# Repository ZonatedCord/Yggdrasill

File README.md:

<div align="center">

# Yggdrasill

**Smart LED plant pot** — custom ESP32 PCB, addressable LEDs, WLED firmware, a modular 3D-printed vase, and a native iOS app with Apple's Liquid Glass design.

</div>

---

## What it is

A tree-shaped plant pot built from three independent pieces that come together into one object:

<table>
<tr>
<td width="33%" valign="top">

### Hardware
`PCB/`

ESP32 board driving WS2812B / SK6812 addressable LEDs, plus the leaf board that carries the LEDs. 5 KiCad projects: 4 base-board projects (dev-kit, bare-chip Rev 1.03, bare-chip Rev 2.0, USB-C) and the leaf (`Foglia`).

</td>
<td width="33%" valign="top">

### 3D print
`3D/`

Modular vase — base, lid, trunk, 3 branches, 9 leaves — joined with bayonet/snap-fit joints. FDM-printable in PETG or PLA. Prototype built in PLA on a Bambu Lab P2S; the supports inside the branches are hard to remove, see [3D/README.md](3D/README.md).

</td>
<td width="33%" valign="top">

### iOS app
`WLED-iOS/`

Liquid Glass redesign (iOS 26) of a WLED controller. mDNS discovery, WebSocket control.

</td>
</tr>
</table>

---

## Assembly preview

<table>
<tr>
<td align="center" width="50%"><b>Leaf insertion</b></td>
<td align="center" width="50%"><b>Branch assembly</b></td>
</tr>
<tr>
<td></td>
<td></td>
</tr>
</table>

---

## Status

**Working prototype built (Oct 2026):** vase, base, lid, 9 leaves and 3 branches printed in PLA on a Bambu Lab P2S, wired with Wago connectors, with 9 LED leaves; the plant lights up. The leaves will be reprinted to hide the visible layer lines.

| Component | Status |
|---|---|
| BaseChipOnly PCB | **Recommended.** Rev 1.03 (`PCB/BaseChipOnly/`) is fabricated and was brought up and tested; it works with workarounds. **Rev 2.0** (`PCB/BaseChipOnly_rev2/`) fixes every bring-up defect, new layout — verified by DRC/ERC and simulation only, **not yet fabricated or tested on hardware** |
| BaseDevKit PCB | Active |
| BaseUSB-C rev0.1 PCB | Early revision |
| Foglia PCB | Active (9 used in the prototype) |
| Modular vase (`3D/STL_stampa/`) | **Prototype built and working** (PLA, Bambu Lab P2S): vase, base, lid, 9 leaves and all 3 branches fit. Joints were tight at first and needed the mating surfaces smoothed. The fit of `TasselloFissaggioPCB.stl` with the PCB in the base is not yet verified. Tip: the supports inside the branches are hard to remove — a dissolvable/dedicated support filament might help (untested); the author cleaned them by hand with a screwdriver and wire. Print plate for the branches in `Rami.3mf`; details in [3D/README.md](3D/README.md) |
| iOS app (Liquid Glass) | In development |

---

## PCB renders

Board renders are generated from the KiCad files.

<table>
<tr>
<td align="center" width="50%"><b>Rev 1.03 &mdash; fabricated, tested</b></td>
<td align="center" width="50%"><b>Rev 2.0 &mdash; not yet fabricated</b></td>
</tr>
<tr>
<td></td>
<td></td>
</tr>
</table>

Bottom side: [Rev 1.03](PCB/BaseChipOnly/render/bottom.png) &middot; [Rev 2.0](PCB/BaseChipOnly_rev2/render/bottom.png). The renders also show the polyfuse and the two buttons (Rev 2.0) as simplified models, not the real components; regenerate them (and the leaf renders) with `python3 PCB/render/make_renders.py` — see [PCB/README.md](PCB/README.md#regenerating-the-renders).

<table align="center">
<tr>
<td align="center"><b>Leaf board (Foglia) &mdash; top</b></td>
<td align="center"><b>Leaf board (Foglia) &mdash; bottom</b></td>
</tr>
<tr>
<td align="center"></td>
<td align="center"></td>
</tr>
</table>

---

## Photos

Photos of the prototype, the electronics and the earlier versions are in the [docs/images/](docs/images/README.md) folder.

---

## What you need

| For | You need |
|---|---|
| The lamp | A 3D printer with about 256 mm of Z height (branches are up to 335 mm long and are printed lying down; prototype: Bambu Lab P2S, 0.4 mm nozzle, PLA) |
| The electronics | A fabricated `BaseChipOnly` PCB (Gerbers in `PCB/<variant>/Esportazione/`), 9 `Foglia` leaf boards, a USB-UART adapter for flashing WLED, a 5 V **4 A** power supply (see power notes in [docs/assembly.md](docs/assembly.md#power-requirements)) |
| Wiring | Thin, long wires and Wago-style splicing connectors (see [docs/3d-printing.md](docs/3d-printing.md#assembly-notes)) |
| Assembly tips | Solder paste stencils for the SMD boards (the leaf board is needed in 9 copies), see [docs/hardware.md](docs/hardware.md#assembly-tips-solder-paste-stencils) |
| PCB editing | **KiCad 9** (the project files are saved with KiCad 9 and do not open in KiCad 8) |
| The app | **Xcode 26** to build (the project is saved with Xcode 26.2); deployment target 16.0 as set in the Xcode project; the Liquid Glass design targets iOS 26 |

## How to build it

1. **Print** the parts from `3D/STL_stampa/` (PLA or PETG, 0.2 mm layers). Orientation, branch plate (`Rami.3mf`), support removal and joint clearances: [docs/3d-printing.md](docs/3d-printing.md) and [3D/README.md](3D/README.md).
2. **Fabricate the PCBs.** Gerbers are in `PCB/<variant>/Esportazione/` (Rev 2.0: `PCB/BaseChipOnly_rev2/Esportazione-2026-09-30/`); upload them to JLCPCB or PCBWay. Variants, BOM and fabrication notes: [docs/hardware.md](docs/hardware.md). The 3D base is designed for `BaseChipOnly` only.
3. **Flash WLED** on the ESP32 and **assemble** the lamp (wiring, base, trunk, branches, leaves, lid): follow [docs/assembly.md](docs/assembly.md) (work in progress). Board details and first power-up: [docs/base-chiponly-pcb.md](docs/base-chiponly-pcb.md).
4. **Control it** from the iOS app below, or from any WLED client.

### iOS app

Build with **Xcode 26** (the project is saved with Xcode 26.2). The app's deployment target is iOS 16.0 as set in the Xcode project; the Liquid Glass styling is the iOS 26 design language.

```bash
git clone --recurse-submodules https://github.com/ZonatedCord/Yggdrasill
open WLED-iOS/wled.xcodeproj
```

> `WLED-iOS/` is a git submodule pointing to the `liquid-glass-redesign` branch of [ZonatedCord/WLED-iOS](https://github.com/ZonatedCord/WLED-iOS) — a fork of [Moustachauve/WLED-iOS](https://github.com/Moustachauve/WLED-iOS) restyled with Apple's Liquid Glass (iOS 26). Already cloned without `--recurse-submodules`? Run `git submodule update --init`. More: [docs/ios-app.md](docs/ios-app.md).

---

## Repository structure

```
Yggdrasill/
├── PCB/               KiCad projects — BaseDevKit, BaseChipOnly (Rev 1.03), BaseChipOnly_rev2 (Rev 2.0), BaseUSB-C_rev0.1, Foglia + footprint library (Impronte/) + render/ (make_renders.py)
├── 3D/                Modular vase — Vaso/ (STEP sources + animations), STL_stampa/ (print-ready STLs + Rami.3mf)
├── WLED-iOS/          iOS app (Liquid Glass, GPL v3) — git submodule → ZonatedCord/WLED-iOS @ liquid-glass-redesign
├── docs/              Hardware, iOS, 3D printing, and assembly documentation
│   └── hardware-reviews/  PCB analysis notes (review + bring-up fixes)
├── LICENSE            CC BY-NC-SA 4.0 (hardware + 3D)
├── LICENSE-NOTICES.md Dual-license clarification
├── CHANGELOG.md
└── CONTRIBUTING.md
```

---

## Documentation

- [Hardware variants & BOM](docs/hardware.md)
- [iOS app architecture & Liquid Glass](docs/ios-app.md)
- [3D printing guide](docs/3d-printing.md) · [3D parts and wiring tips](3D/README.md)
- [Assembly guide](docs/assembly.md)
- [PCB variants and render script](PCB/README.md)
- [BaseChipOnly — how the board works](docs/base-chiponly-pcb.md) · [Rev 2.0: tests and changes](PCB/BaseChipOnly_rev2/README.md)
- [BaseChipOnly hardware review](docs/hardware-reviews/base-chiponly-review.md) · [bring-up defects & fixes](docs/hardware-reviews/base-chiponly-fixes.md)
- [Changelog](CHANGELOG.md) · [Contributing](CONTRIBUTING.md)

---

## License

**Hardware & 3D models** (`PCB/`, `3D/`, `docs/`) — Creative Commons Attribution-NonCommercial-ShareAlike 4.0 International, Copyright (c) 2025 Marco Barlera. Free for personal and maker use; commercial use requires explicit written permission.
See [LICENSE](LICENSE) · [creativecommons.org/licenses/by-nc-sa/4.0](https://creativecommons.org/licenses/by-nc-sa/4.0/)

**iOS app** (`WLED-iOS/`) — GNU General Public License v3.0, inherited from [Moustachauve/WLED-iOS](https://github.com/Moustachauve/WLED-iOS). Copyleft; cannot be changed.
See [WLED-iOS/LICENSE](WLED-iOS/LICENSE)

Full dual-license details: [LICENSE-NOTICES.md](LICENSE-NOTICES.md)

---

<div align="center">

**Marco Barlera** — [marcobarlera.com](https://marcobarlera.com) — barleramarco05@gmail.com

Commercial licensing inquiries: contact via email.

</div>

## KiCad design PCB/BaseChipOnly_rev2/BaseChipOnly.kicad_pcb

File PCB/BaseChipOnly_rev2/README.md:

# BaseChipOnly — HW Rev 2.0

Base board of the Yggdrasill lamp: ESP32-WROOM-32U running WLED, 5 V input, drives the 9 leaf boards (`../Foglia`, 15 WS2812B each, wired in parallel). This is the second revision of `../BaseChipOnly` (rev 1.03, the board that was actually fabricated and brought up).

How the board works, power budget and WLED settings: [`docs/base-chiponly-pcb.md`](../../docs/base-chiponly-pcb.md).

> ## ⚠️ Limitation: verified on paper, not on a real board
>
> Rev 2.0 has **not been fabricated or assembled yet**. Everything below was checked with design-rule tools, file cross-checks and circuit simulation — nothing has been measured on hardware. Simulations use component models (TI's LM2596 model, generic MMBT3904/SS34/LED models) and assumptions (cable resistance, wire length to the leaves, capacitor derating) that may differ from reality. The firmware/boot of the ESP32 cannot be simulated: "it boots" means EN and IO0 reach the right levels at the right time.
>
> Before trusting it, build one board and follow the **first power-up procedure** in `docs/base-chiponly-pcb.md`, then test the auto-reset with `esptool.py flash_id`.

## Status

| | |
|---|---|
| Schematic | complete, ERC 0 errors |
| PCB | complete, DRC 0 errors, schematic ↔ PCB parity clean |
| Fab files | `Esportazione-2026-09-30/` (Gerbers, drill, BOM with MPNs, pick-and-place, assembly PDF with values, schematic PDF, 3D preview) |
| Fabricated | **no** |
| Tested on hardware | **no** |

## Tests performed (all theoretical)

| Test | Tool | Result |
|---|---|---|
| Electrical rules check | KiCad ERC | 0 errors |
| Design rules check + schematic parity | KiCad DRC `--schematic-parity` | 0 errors, 0 unconnected, 0 parity issues (12 known items: 0.2 mm thermal-via drills of the ESP32 footprint, same as rev 1.03) |
| Copper vs schematic | Gerber X2 pad attributes of the exported front copper | 120 / 120 pads on the right net |
| Pinout of every active part vs datasheet | netlist + datasheets | 0 mismatches (LM2596S-ADJ, USBLC6-2SC6, MMBT3904, diodes, polarised caps, connectors, ESP32) |
| ESP32 strapping pins | netlist review | IO0 pull-up + BOOT; IO2/IO12 floating (download mode OK, 3.3 V flash); IO5/IO15 internal pull-ups |
| Trace current capacity | IPC-2221, 1 oz outer layer, +10 °C | all power traces above their current (e.g. +5V bus 3 mm → 5.3 A for ~3.3 A) |
| Fab limits | JLCPCB rules | tracks ≥ 0.2 mm, vias 0.6/0.3, copper ≥ 1 mm from edge, silkscreen ≥ 0.8 mm / 0.15 mm |
| Mechanical / visual | KiCad 3D render | polarity marks, orientation, ≥ ~1 mm between parts in the regulator block, ≥ 1.1 mm from the ESP32 |
| Auto-reset (both esptool sequences) | ngspice | enters download mode; serial monitor does not reset the board |
| Power-on EN timing | ngspice | EN rises 13.7 ms after 3.3 V (spec ≥ 50 µs) |
| 3.3 V regulator: nominal, LEDs at 3 A, minimum input, start-up | ngspice + Texas Instruments LM2596 model (SNVMA65, credited in `LICENSE-NOTICES.md`) | 3.28 V, ≥ 3.21 V worst case; needs ≥ ~4.5 V at its input |
| Status LED current | ngspice | 4.6–6.7 mA |
| LED data line to 9 parallel leaves | ngspice | clean ~370/770 ns pulses with R5 = 100 Ω |

Re-run the checks with `./verifica.sh` (ERC + DRC/parity + fab export + Gerber cross-check). Simulations: `simulazioni/README.md` (run `simulazioni/models/get_lm2596_model.sh` once to fetch the TI model).

## Changes from rev 1.03

**Bugs fixed (all seen during the rev 1.03 bring-up)**

| Rev 1.03 | Rev 2.0 |
|---|---|
| D2 (SS34 catch diode) reversed — shorts the regulator switch node | correct polarity, silkscreen matches |
| D1 (status LED) reversed | correct polarity; GND via moved out of the pad (likely cause of the dark LED) |
| Auto-reset wired wrong: both emitters to GND — idle adapter held the ESP32 in reset, esptool could never enter download mode | standard cross-coupled DTR/RTS circuit, like ESP32 DevKit boards |
| No BOOT / RESET buttons | SW1 BOOT, SW2 RESET (C&K PTS810), centred on the top edge |
| L1 1008 inductor, no value — burned out | Bourns SRN6045TA-101M, 100 µH, Isat 1.33 A |
| Polyfuse 12 A in 0603 — protects nothing | Bourns MF-LSMF400/12X, 4 A hold, 2920 |
| U3 (USBLC6) GND pin unconnected — no ESD protection | GND connected, VBUS to +5V (ST reference circuit) |
| TVS: bidirectional symbol, SMF5.0A part on an SMA footprint | SMAJ5.0A, unidirectional, matches the footprint |
| Reference and Value swapped on the PCB, footprints not linked to the schematic | fixed: correct BOM / pick-and-place, Update-PCB-from-Schematic works |
| 12 ESP32 thermal vias with no net | tied to GND |
| Silkscreen typo "GDN" | "GND" |

**Improvements**

- COUT2 220 µF tantalum (Kyocera AVX TPSC227M006R0100) next to the 47 µF MLCC, for LM2596 loop stability.
- C4 100 nF → 1 µF (EN delay, Espressif guideline) — from the simulations.
- R5 470 Ω → 100 Ω (clean data pulses to the 9 parallel leaves) — from the simulations.
- Auto-reset transistors specified as MMBT3904 (no part number before).
- +3V3 traces 0.2 → 0.5–1.0 mm; SW node 1.2–1.5 mm.
- New layout: functional blocks, regulator with a short switching loop and room for hand soldering, solid GND plane on the back, no via-in-pad on GND, silkscreen to fab minimums, HW Rev 2.0 printed on the board.

**Unchanged on purpose:** board outline and mounting holes (the printed base and `TasselloFissaggioPCB.stl` still fit), J1 barrel jack, J2 terminal, J3 programming header (external USB-UART adapter, no USB-C), ESP32 position, C1, LED data on GPIO13.

## Known limits

- The LM2596 needs ≥ ~4.5 V at its input at 500 mA: use a good 5 V 4 A PSU with a short, thick cable and keep the WLED current limiter at 3000 mA.
- The USB-UART adapter must break out **DTR and RTS** at 3.3 V for the auto-reset; otherwise use BOOT/RESET.
- Button reachability inside the printed base not checked.

## Folder contents

| Path | What |
|---|---|
| `BaseChipOnly.kicad_pro/.kicad_sch/.kicad_pcb` | KiCad 9 project |
| `Esportazione-2026-09-30/` | fabrication files for rev 2.0 |
| `verifica.sh` | all automatic checks in one go |
| `simulazioni/` | ngspice decks, plots, results |
| `FIX_LOG.md` | session-by-session log of every change (Italian) |
| `BaseChipOnly-backups/fixpcb_2026-09-30.py`, `relayout-work/relayout.py`, `build.sh` | scripts that generated the PCB (record of every edit; their input boards live in the local, git-ignored `BaseChipOnly-backups/`) |
| `FileImpronte/` | ESP32-WROOM-32U symbol / footprint / 3D model |

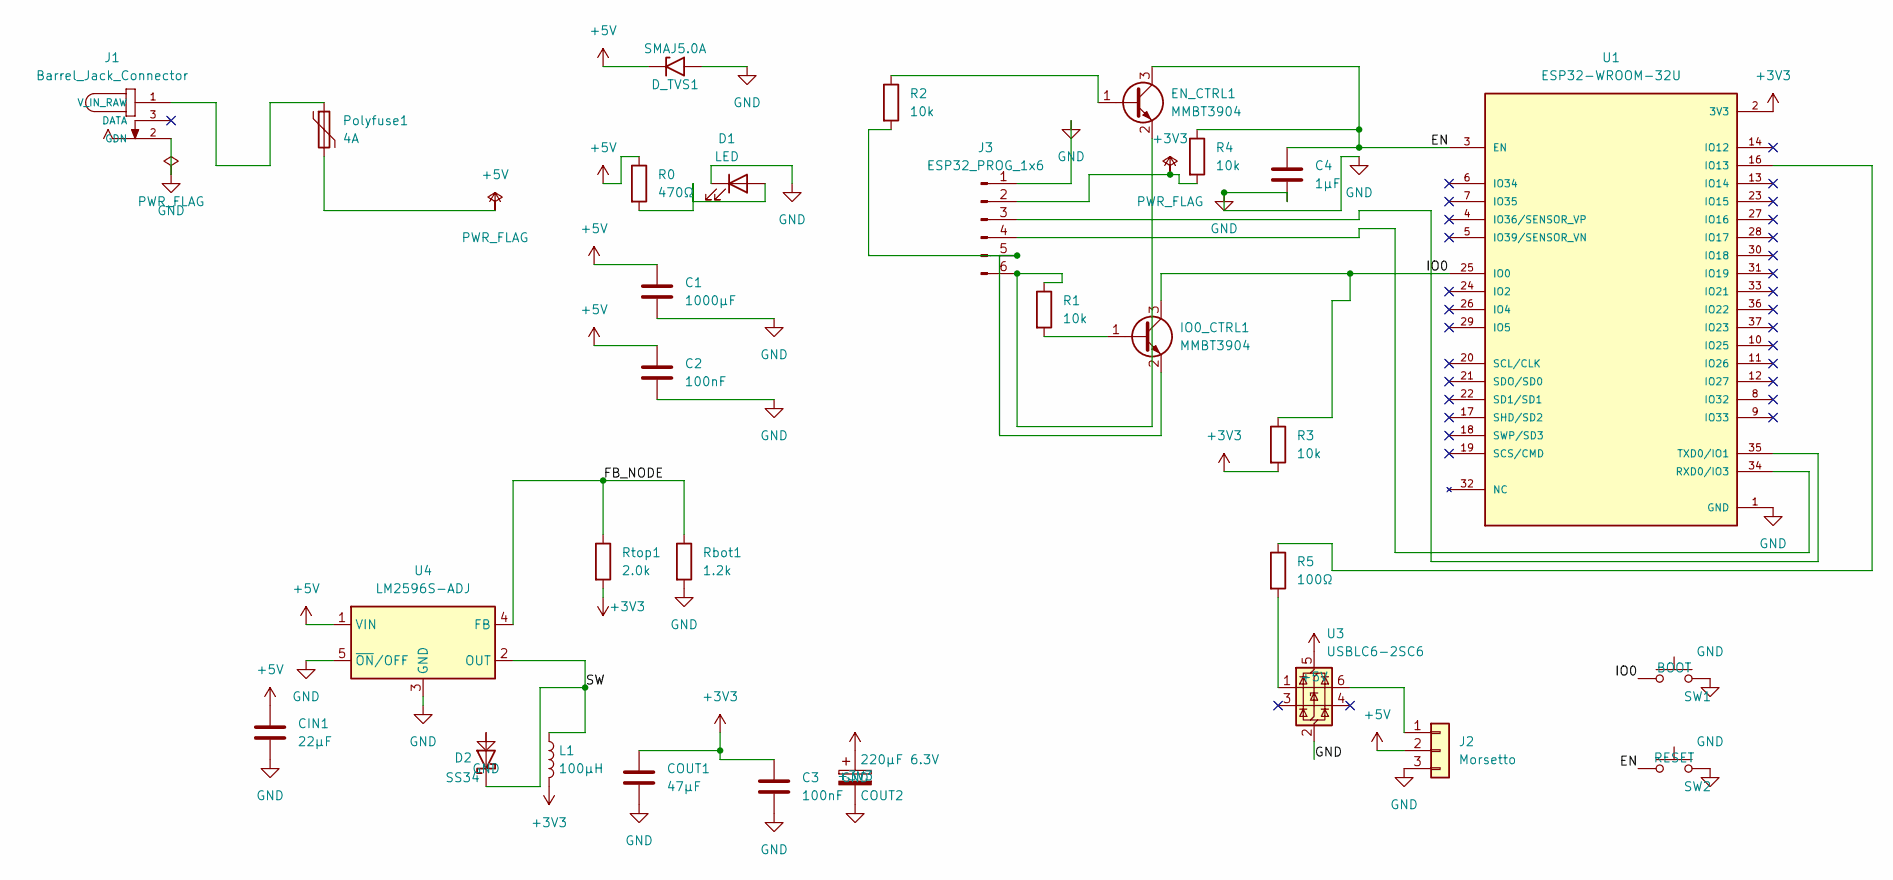
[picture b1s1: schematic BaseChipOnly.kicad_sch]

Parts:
C1: 1000µF; CP_Radial_D10.0mm_P5.00mm
C2, C3: 100nF; C_0805_2012Metric_Pad1.18x1.45mm_HandSolder
C4: 1µF; C_0603_1608Metric_Pad1.08x0.95mm_HandSolder
CIN1: 22µF; C_0805_2012Metric_Pad1.18x1.45mm_HandSolder
COUT1: 47µF; C_0805_2012Metric_Pad1.18x1.45mm_HandSolder
COUT2: 220µF 6.3V; CP_EIA-6032-28_Kemet-C_HandSolder; MPN TPSC227M006R0100
D1: LED; LED_0805_2012Metric_Pad1.15x1.40mm_HandSolder
D2: SS34; D_SMA
D_TVS1: SMAJ5.0A; D_SMA; MPN SMAJ5.0A
EN_CTRL1: MMBT3904; SOT-23; MPN MMBT3904
IO0_CTRL1: MMBT3904; SOT-23; MPN MMBT3904
J1: Barrel_Jack_Connector; BarrelJack
J2: Morsetto; Morsetto_3_Vie
J3: ESP32_PROG_1x6; PinHeader_1x06_P2.54mm_Vertical
L1: 100µH; L_Bourns_SRN6045TA; MPN SRN6045TA-101M
Polyfuse1: 4A; Fuse_2920_7451Metric_Pad2.10x5.45mm_HandSolder; MPN MF-LSMF400/12X
R0: 470Ω; R_0805_2012Metric_Pad1.20x1.40mm_HandSolder
R1, R2, R3, R4: 10k; R_0603_1608Metric_Pad0.98x0.95mm_HandSolder
R5: 100Ω; R_0805_2012Metric_Pad1.20x1.40mm_HandSolder
Rbot1: 1.2k; R_0805_2012Metric_Pad1.20x1.40mm_HandSolder
Rtop1: 2.0k; R_0805_2012Metric_Pad1.20x1.40mm_HandSolder
SW1: BOOT; SW_SPST_PTS810; MPN PTS810 SJM 250 SMTR LFS
SW2: RESET; SW_SPST_PTS810; MPN PTS810 SJM 250 SMTR LFS
U1: ESP32-WROOM-32U; XCVR_ESP32-WROOM-32U; PARTREV 2.4
U3: USBLC6-2SC6; SOT-23-6_Handsoldering
U4: LM2596S-ADJ; TO-263-5_TabPin3

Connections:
+3V3: C3.1, COUT1.1, COUT2.1, J3.2 (3V3), L1.2, R3.2, R4.2, Rtop1.2, U1.2 (3V3)
+5V: C1.1, C2.1, CIN1.1, D_TVS1.1 (A1), J2.2, Polyfuse1.2, R0.1, U3.5 (VBUS), U4.1 (VIN)
/EN: C4.1, EN_CTRL1.3 (C), R4.1, SW2.1, U1.3 (EN)
/FB_NODE: Rbot1.1, Rtop1.1, U4.4 (FB)
/IO0: IO0_CTRL1.3 (C), R3.1, SW1.1, U1.25 (IO0)
/SW: D2.1 (K), L1.1, U4.2 (OUT)
GND: C1.2, C2.2, C3.2, C4.2, CIN1.2, COUT1.2, COUT2.2, D1.1 (K), D2.2 (A), D_TVS1.2 (A2), J1.2 (GDN), J2.3, J3.1 (GND), Rbot1.2, SW1.2, SW2.2, U1.1 (GND), U1.15 (GND), U1.38 (GND), U1.39_1 (GND), U1.39_2 (GND), U1.39_3 (GND), U1.39_4 (GND), U1.39_5 (GND), U1.39_6 (GND), U1.39_7 (GND), U1.39_8 (GND), U1.39_9 (GND), U3.2 (GND), U4.3 (GND), U4.5 (~ON/OFF)
unnamed: D1.2 (A), R0.2
unnamed: EN_CTRL1.1 (B), R2.1
unnamed: EN_CTRL1.2 (E), J3.6 (RTS), R1.1
unnamed: IO0_CTRL1.1 (B), R1.2
unnamed: IO0_CTRL1.2 (E), J3.5 (DTR), R2.2
unnamed: J1.1 (V_IN_RAW), Polyfuse1.1
unnamed: J2.1, U3.6 (I/O1)
unnamed: J3.4 (RX0), U1.34 (RXD0/IO3)
unnamed: J3.3 (TX0), U1.35 (TXD0/IO1)
unnamed: R5.2, U3.1 (I/O1)
unnamed: R5.1, U1.16 (IO13)

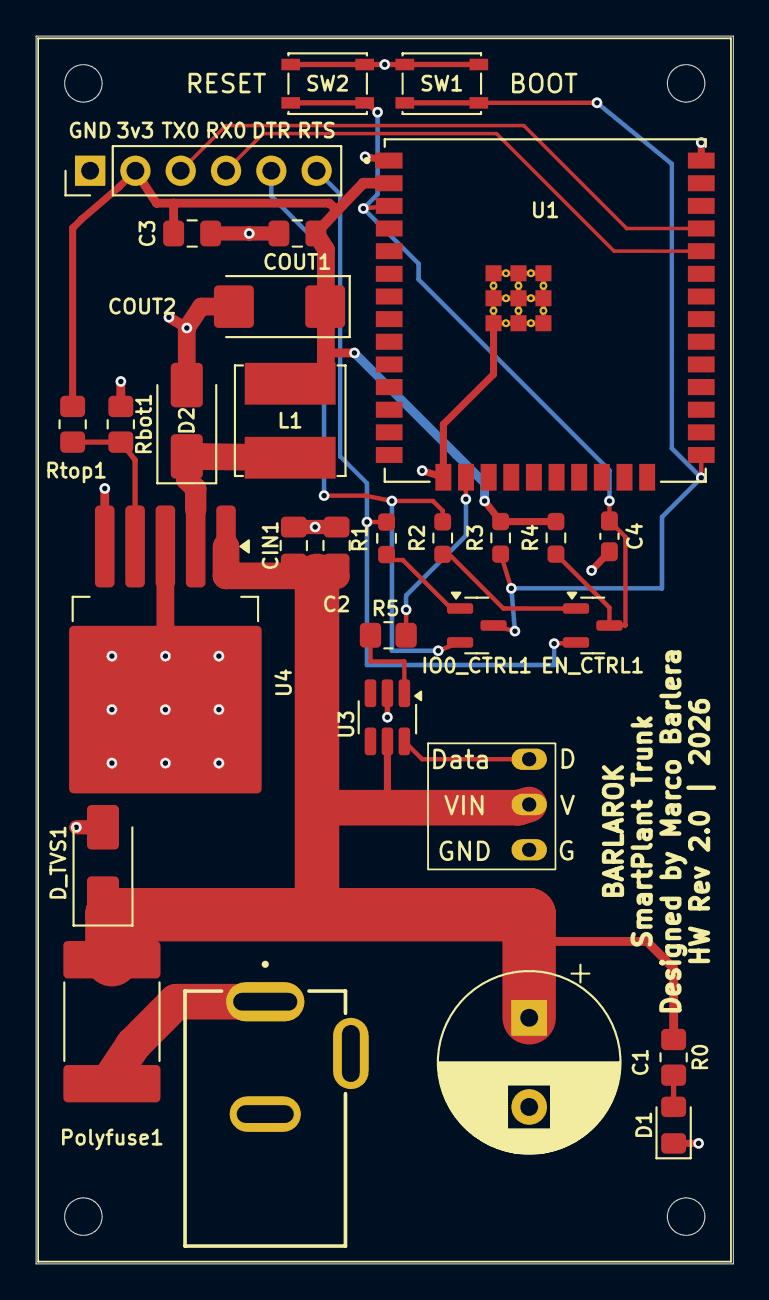
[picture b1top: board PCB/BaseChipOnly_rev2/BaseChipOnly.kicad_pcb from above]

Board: 2 copper layers, 39.1 x 68.8 mm, 34 parts (0 on the bottom side), 18 nets.

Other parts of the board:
H1, H2, H3, H4: MountingHole_2.1mm

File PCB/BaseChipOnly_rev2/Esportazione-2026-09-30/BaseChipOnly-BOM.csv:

"Reference","Value","Footprint","MPN","Manufacturer","QUANTITY"
"C1","1000µF","Capacitor_THT:CP_Radial_D10.0mm_P5.00mm","","","1"
"C2,C3","100nF","Capacitor_SMD:C_0805_2012Metric_Pad1.18x1.45mm_HandSolder","","","2"
"C4","1µF","Capacitor_SMD:C_0603_1608Metric_Pad1.08x0.95mm_HandSolder","","","1"
"CIN1","22µF","Capacitor_SMD:C_0805_2012Metric_Pad1.18x1.45mm_HandSolder","","","1"
"COUT1","47µF","Capacitor_SMD:C_0805_2012Metric_Pad1.18x1.45mm_HandSolder","","","1"
"COUT2","220µF 6.3V","Capacitor_Tantalum_SMD:CP_EIA-6032-28_Kemet-C_HandSolder","TPSC227M006R0100","Kyocera AVX","1"
"D1","LED","LED_SMD:LED_0805_2012Metric_Pad1.15x1.40mm_HandSolder","","","1"
"D2","SS34","Diode_SMD:D_SMA","","","1"
"D_TVS1","SMAJ5.0A","Diode_SMD:D_SMA","SMAJ5.0A","Littelfuse (o equivalente)","1"
"EN_CTRL1,IO0_CTRL1","MMBT3904","Package_TO_SOT_SMD:SOT-23","MMBT3904","onsemi / Nexperia (any MMBT3904, SOT-23 B-E-C)","2"
"J1","Barrel_Jack_Connector","USBC:BarrelJack","","","1"
"J2","Morsetto","USBC:Morsetto_3_Vie","","","1"
"J3","ESP32_PROG_1x6","Connector_PinHeader_2.54mm:PinHeader_1x06_P2.54mm_Vertical","","","1"
"L1","100µH","Inductor_SMD:L_Bourns_SRN6045TA","SRN6045TA-101M","Bourns","1"
"Polyfuse1","4A","Fuse:Fuse_2920_7451Metric_Pad2.10x5.45mm_HandSolder","MF-LSMF400/12X","Bourns","1"
"R0","470Ω","Resistor_SMD:R_0805_2012Metric_Pad1.20x1.40mm_HandSolder","","","1"
"R1-R4","10k","Resistor_SMD:R_0603_1608Metric_Pad0.98x0.95mm_HandSolder","","","4"
"R5","100Ω","Resistor_SMD:R_0805_2012Metric_Pad1.20x1.40mm_HandSolder","","","1"
"Rbot1","1.2k","Resistor_SMD:R_0805_2012Metric_Pad1.20x1.40mm_HandSolder","","","1"
"Rtop1","2.0k","Resistor_SMD:R_0805_2012Metric_Pad1.20x1.40mm_HandSolder","","","1"
"SW1","BOOT","Button_Switch_SMD:SW_SPST_PTS810","PTS810 SJM 250 SMTR LFS","C&K","1"
"SW2","RESET","Button_Switch_SMD:SW_SPST_PTS810","PTS810 SJM 250 SMTR LFS","C&K","1"
"U1","ESP32-WROOM-32U","USBC:XCVR_ESP32-WROOM-32U","","","1"
"U3","USBLC6-2SC6","Package_TO_SOT_SMD:SOT-23-6_Handsoldering","","","1"
"U4","LM2596S-ADJ","Package_TO_SOT_SMD:TO-263-5_TabPin3","","","1"

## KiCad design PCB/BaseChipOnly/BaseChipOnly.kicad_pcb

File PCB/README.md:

# PCB — Hardware Variants

KiCad 9 projects (saved with KiCad 9; KiCad 8 cannot open them). ESP32 + WS2812B/SK6812 addressable LEDs.

| Folder | Description | Status | Gerbers |
|---|---|---|---|
| `BaseDevKit/` | ESP32 dev kit carrier | Active | `BaseDevKit/Esportazione/` |
| `BaseChipOnly/` | Bare ESP32-WROOM-32, compact — rev 1.03 as fabricated | Superseded by the next rev | `BaseChipOnly/Esportazione/` |
| `BaseChipOnly_rev2/` | BaseChipOnly HW Rev 2.0: all bring-up fixes + new layout (see its `README.md`) | Verified on paper (DRC/ERC/simulation), not yet fabricated | `BaseChipOnly_rev2/Esportazione-2026-09-30/` |
| `BaseUSB-C_rev0.1/` | USB-C power input | Early rev | — |
| `Foglia/` | Leaf-shaped decorative board | Active | `Foglia/Esportazione/` |
| `Impronte/` | Custom KiCad footprint library | Library | — |

For fabrication details and BOM see [docs/hardware.md](../docs/hardware.md).

How BaseChipOnly works: [docs/base-chiponly-pcb.md](../docs/base-chiponly-pcb.md). For the design review see [docs/hardware-reviews/base-chiponly-review.md](../docs/hardware-reviews/base-chiponly-review.md).

## Regenerating the renders

```bash
python3 PCB/render/make_renders.py
```

The script regenerates top and bottom renders of BaseChipOnly Rev 1.03, Rev 2.0 and the leaf board Foglia (standard library only; it finds `kicad-cli` in the PATH or in `/Applications/KiCad/KiCad.app/Contents/MacOS`).

KiCad lacks some 3D models, so the script adds them to temporary copies of the boards: the ESP32 module and the barrel jack (both revisions) and, for Rev 2.0, the 2920 polyfuse and the PTS810 buttons as simplified hand-made models (`PCB/render/models/`). The board files are never modified.

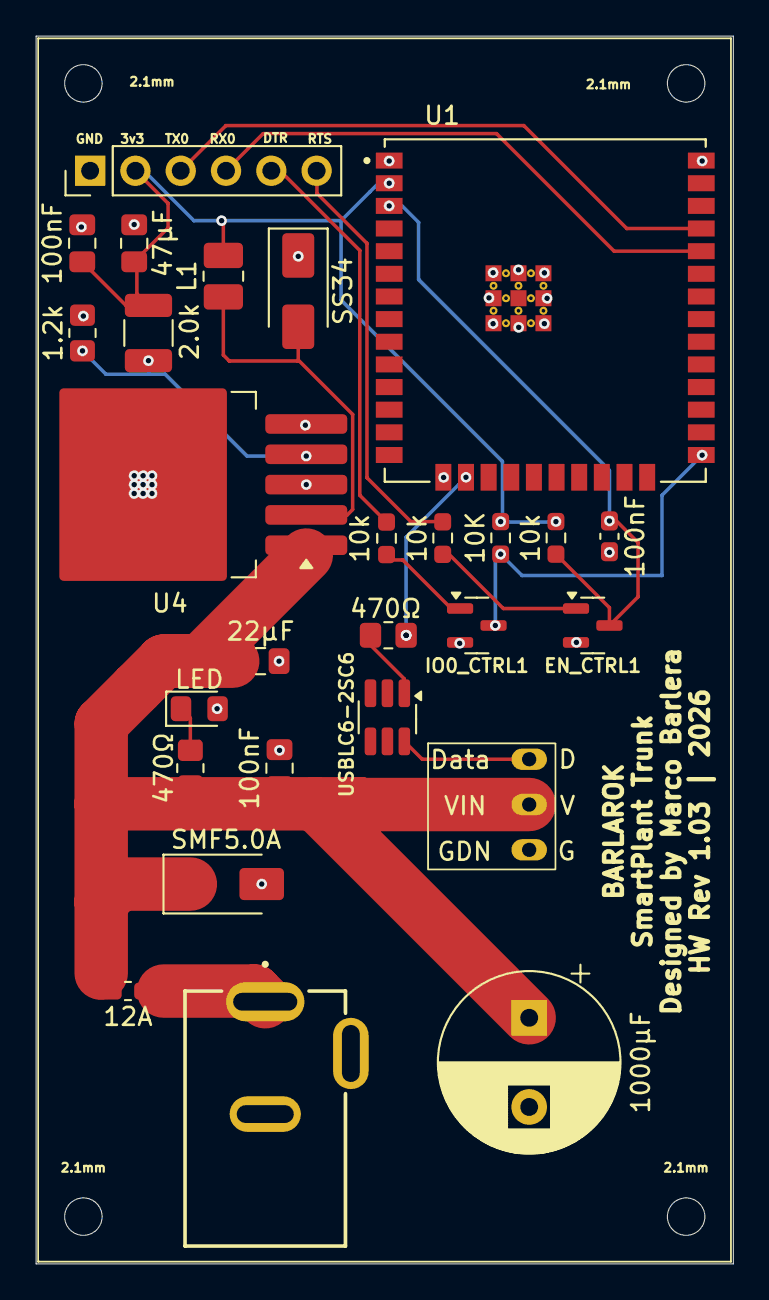
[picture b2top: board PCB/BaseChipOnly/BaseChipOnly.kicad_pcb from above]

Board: 2 copper layers, 39.1 x 68.8 mm, 31 parts (0 on the bottom side), 18 nets.

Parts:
1.2k: Rbot; R_0805_2012Metric_Pad1.20x1.40mm_HandSolder
2.0k: Rtop1; R_1210_3225Metric_Pad1.30x2.65mm_HandSolder
2.1mm, 2.1mm#2, 2.1mm#3, 2.1mm#4: MountingHole_2.1mm
10K: R3; R_0603_1608Metric_Pad0.98x0.95mm_HandSolder
10k: R4; R_0603_1608Metric_Pad0.98x0.95mm_HandSolder
10k#2: R1; R_0603_1608Metric_Pad0.98x0.95mm_HandSolder
10k#3: R2; R_0603_1608Metric_Pad0.98x0.95mm_HandSolder
12A: Polyfuse; Fuse_0603_1608Metric_Pad1.05x0.95mm_HandSolder
22µF: CIN1; C_0805_2012Metric_Pad1.18x1.45mm_HandSolder
47µF: COUT1; C_0805_2012Metric_Pad1.18x1.45mm_HandSolder
100nF: C2; C_0805_2012Metric_Pad1.18x1.45mm_HandSolder
100nF#2: C3; C_0805_2012Metric_Pad1.18x1.45mm_HandSolder
100nF#3: C4; C_0603_1608Metric_Pad1.08x0.95mm_HandSolder
470Ω: R0; R_0805_2012Metric_Pad1.20x1.40mm_HandSolder
470Ω#2: R5; R_0805_2012Metric_Pad1.20x1.40mm_HandSolder
1000µF: C1; CP_Radial_D10.0mm_P5.00mm
EN_CTRL1: Q_NPN_BEC; SOT-23
IO0_CTRL1: Q_NPN_BEC; SOT-23
J1: Barrel_Jack_Connector; BarrelJack
J2: Morsetto; Morsetto_3_Vie
J3: ESP32_PROG_1x6; PinHeader_1x06_P2.54mm_Vertical
L1: L; L_1008_2520Metric_Pad1.43x2.20mm_HandSolder
LED: D1; LED_0805_2012Metric_Pad1.15x1.40mm_HandSolder
SMF5.0A: DTVS; D_SMA
SS34: D2; D_SMA
U1: ESP32-WROOM-32U; XCVR_ESP32-WROOM-32U
U4: LM2596S-ADJ; TO-263-5_TabPin3
USBLC6-2SC6: USBLC6-2SC6; SOT-23-6_Handsoldering

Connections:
+3V3: 2.0k.2, 10K.2, 10k.2, 47µF.1, 100nF#2.1, J3.2 (3V3), L1.2, U1.2 (3V3)
+5V: 12A.2, 22µF.1, 100nF.1, 470Ω.1, 1000µF.1, J2.2, SMF5.0A.1 (A1), U4.1 (VIN)
/FB_NODE: 1.2k.1, 2.0k.1, U4.4 (FB)
/SW: L1.1, SS34.2 (A), U4.2 (OUT)
GND: 1.2k.2, 22µF.2, 47µF.2, 100nF.2, 100nF#2.2, 100nF#3.2, 1000µF.2, EN_CTRL1.2 (E), IO0_CTRL1.2 (E), J1.2 (GDN), J2.3, J3.1 (GND), LED.2 (A), SMF5.0A.2 (A2), SS34.1 (K), U1.1 (GND), U1.15 (GND), U1.38 (GND), U1.39_1 (GND), U1.39_2 (GND), U1.39_3 (GND), U1.39_4 (GND), U1.39_5 (GND), U1.39_6 (GND), U1.39_7 (GND), U1.39_8 (GND), U1.39_9 (GND), U4.3 (GND), U4.5 (~ON/OFF)
unnamed: 470Ω.2, LED.1 (K)
unnamed: 10k#3.1, EN_CTRL1.1 (B)
unnamed: 10k.1, 100nF#3.1, EN_CTRL1.3 (C), U1.3 (EN)
unnamed: 10k#2.2, IO0_CTRL1.1 (B)
unnamed: 10K.1, IO0_CTRL1.3 (C), U1.25 (IO0)
unnamed: 12A.1, J1.1 (V_IN_RAW)
unnamed: J2.1, USBLC6-2SC6.6 (I/O1)
unnamed: 10k#2.1, J3.5 (DTR)
unnamed: 10k#3.2, J3.6 (RTS)
unnamed: J3.4 (RX0), U1.34 (RXD0/IO3)
unnamed: J3.3 (TX0), U1.35 (TXD0/IO1)
unnamed: 470Ω#2.2, USBLC6-2SC6.1 (I/O1)
unnamed: 470Ω#2.1, U1.16 (IO13)

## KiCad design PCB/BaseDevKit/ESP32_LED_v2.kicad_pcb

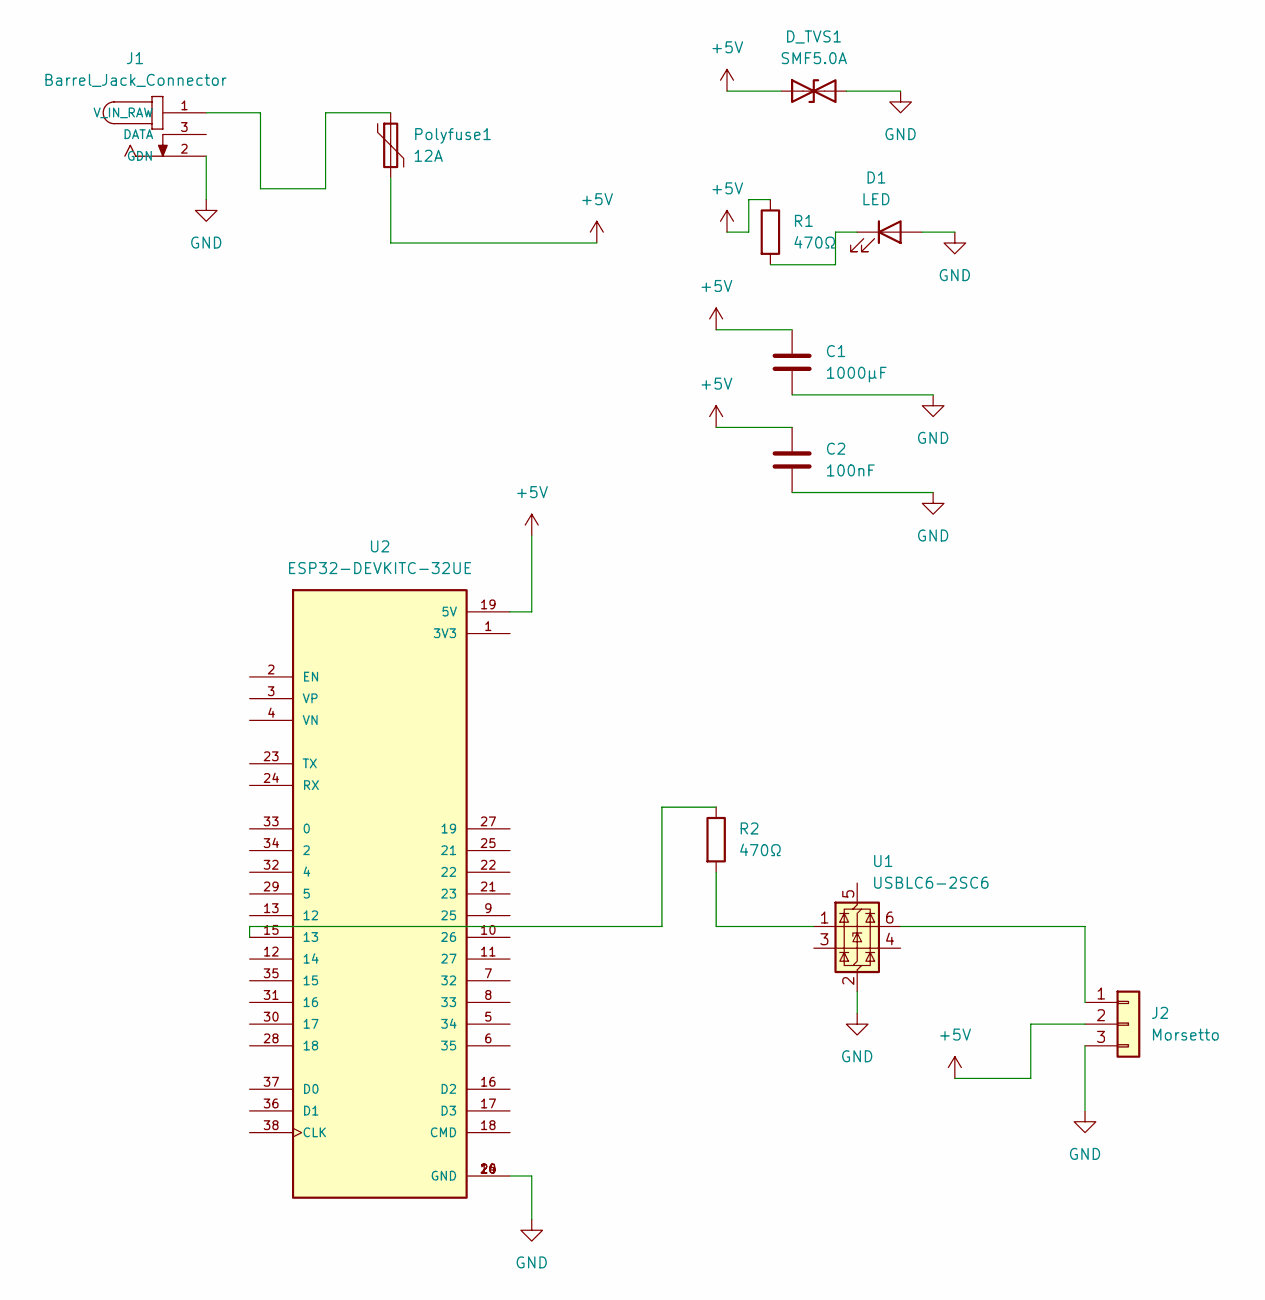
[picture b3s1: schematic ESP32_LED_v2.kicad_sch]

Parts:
C1: 1000µF; CP_Radial_D10.0mm_P5.00mm
C2: 100nF; C_0805_2012Metric_Pad1.18x1.45mm_HandSolder
D1: LED; LED_0402_1005Metric
D_TVS1: SMF5.0A; D_SMA
J1: Barrel_Jack_Connector; BarrelJack
J2: Morsetto; Morsetto_3_Vie
Polyfuse1: 12A; Fuse_0603_1608Metric_Pad1.05x0.95mm_HandSolder
R1, R2: 470Ω; R_0805_2012Metric_Pad1.20x1.40mm_HandSolder
U1: USBLC6-2SC6; SOT-23-6_Handsoldering
U2: ESP32-DEVKITC-32UE; ESPRESSIF_ESP32-DEVKITC-32UE

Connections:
+5V: C1.1, C2.1, D_TVS1.1 (A1), J2.2, Polyfuse1.2, R1.1, U2.19 (5V)
GND: C1.2, C2.2, D1.2 (A), D_TVS1.2 (A2), J1.2 (GDN), J2.3, U1.2 (GND), U2.14 (GND), U2.20 (GND), U2.26 (GND)
unnamed: D1.1 (K), R1.2
unnamed: J1.1 (V_IN_RAW), Polyfuse1.1
unnamed: J2.1, U1.6 (I/O1)
unnamed: R2.2, U1.1 (I/O1)
unnamed: R2.1, U2.15 (13)

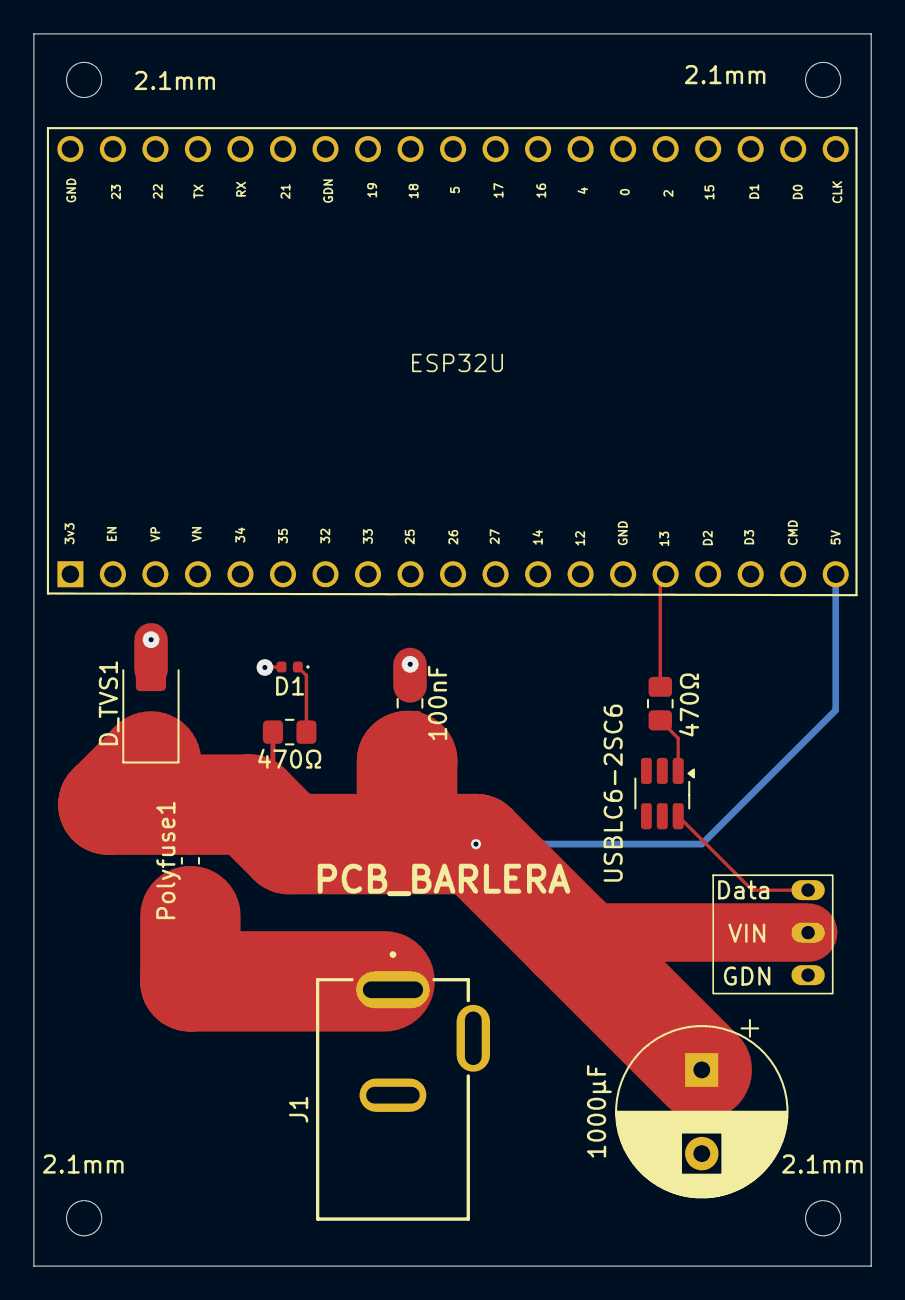
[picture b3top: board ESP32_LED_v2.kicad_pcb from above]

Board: 2 copper layers, 50.0 x 73.6 mm, 15 parts (0 on the bottom side), 7 nets.

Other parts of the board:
2.1mm, 2.1mm#2, 2.1mm#3, 2.1mm#4: MountingHole_2.1mm

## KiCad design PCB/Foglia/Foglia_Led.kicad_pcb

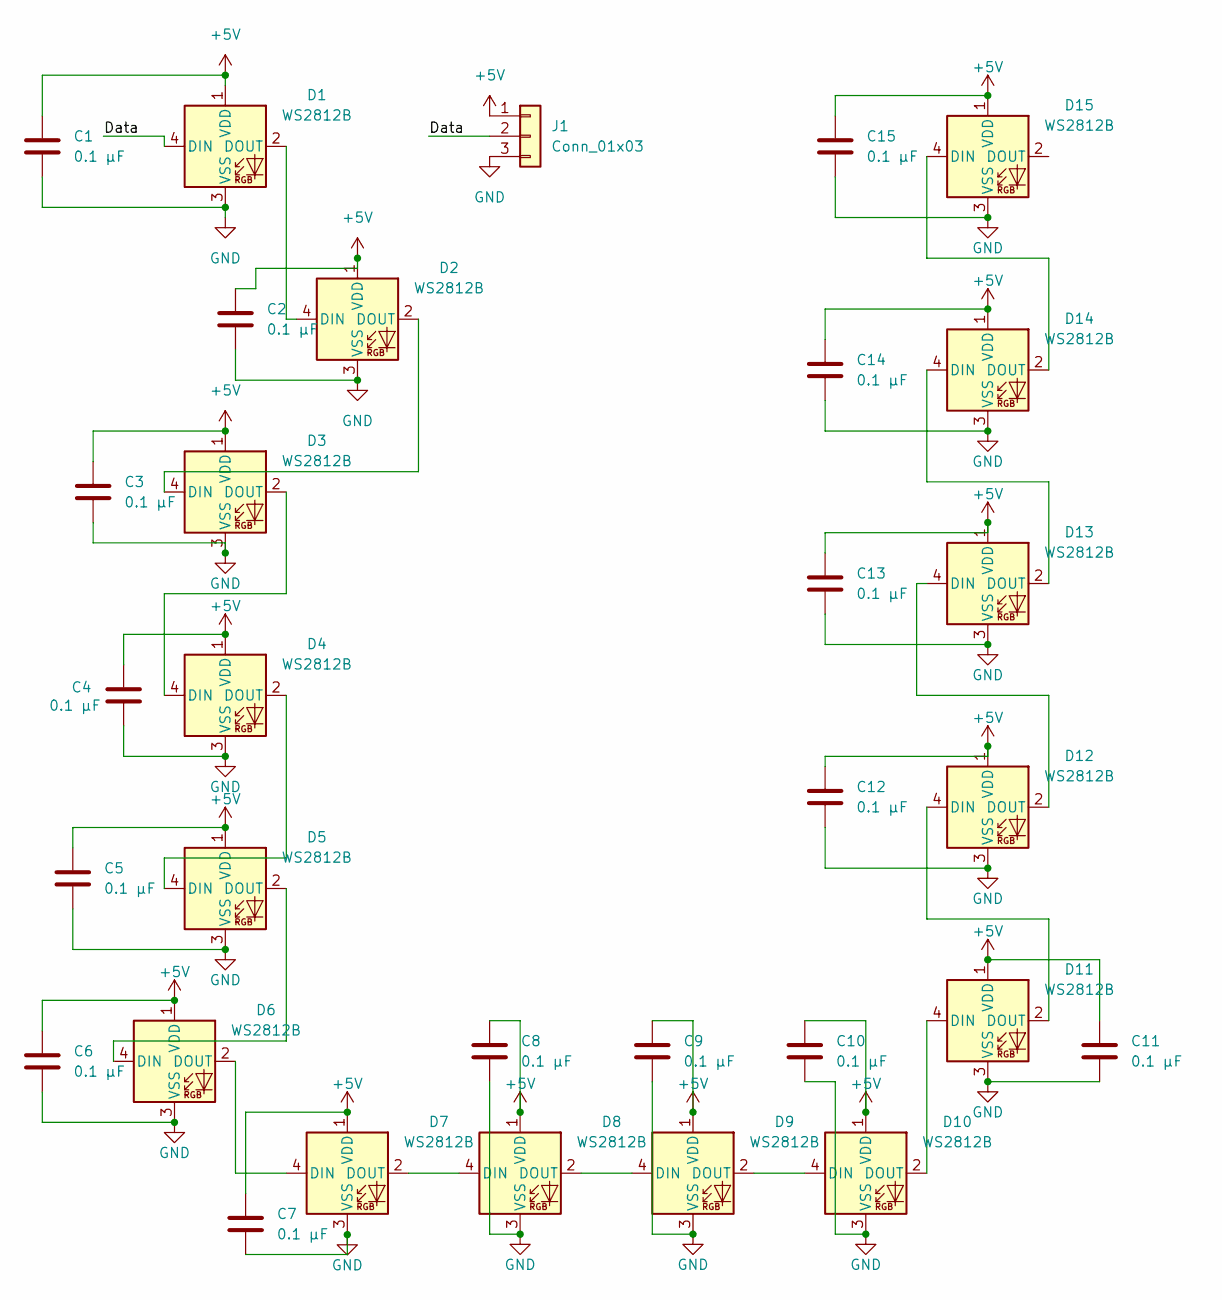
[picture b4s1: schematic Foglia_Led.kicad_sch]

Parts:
C1, C2, C3, C4, C5, C6, C7, C8, C9, C10, C11, C12, C13, C14, C15: 0.1 µF; C_0603_1608Metric_Pad1.08x0.95mm_HandSolder
D1, D2, D3, D4, D5, D6, D7, D9, D10, D11, D12, D13, D14, D15: WS2812B; LED_WS2812B_PLCC4_5.0x5.0mm_P3.2mm
D8: WS2812B; Led_Verticale
J1: Conn_01x03; Pad_LEd

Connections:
+5V: C1.1, C2.1, C3.1, C4.1, C5.1, C6.1, C7.1, C8.1, C9.1, C10.1, C11.1, C12.1, C13.1, C14.1, C15.1, D1.1 (VDD), D2.1 (VDD), D3.1 (VDD), D4.1 (VDD), D5.1 (VDD), D6.1 (VDD), D7.1 (VDD), D8.1 (VDD), D9.1 (VDD), D10.1 (VDD), D11.1 (VDD), D12.1 (VDD), D13.1 (VDD), D14.1 (VDD), D15.1 (VDD), J1.1
/Data: D1.4 (DIN), J1.2
GND: C1.2, C2.2, C3.2, C4.2, C5.2, C6.2, C7.2, C8.2, C9.2, C10.2, C11.2, C12.2, C13.2, C14.2, C15.2, D1.3 (VSS), D2.3 (VSS), D3.3 (VSS), D4.3 (VSS), D5.3 (VSS), D6.3 (VSS), D7.3 (VSS), D8.3 (VSS), D9.3 (VSS), D10.3 (VSS), D11.3 (VSS), D12.3 (VSS), D13.3 (VSS), D14.3 (VSS), D15.3 (VSS), J1.3
unnamed: D1.2 (DOUT), D2.4 (DIN)
unnamed: D2.2 (DOUT), D3.4 (DIN)
unnamed: D3.2 (DOUT), D4.4 (DIN)
unnamed: D4.2 (DOUT), D5.4 (DIN)
unnamed: D5.2 (DOUT), D6.4 (DIN)
unnamed: D6.2 (DOUT), D7.4 (DIN)
unnamed: D7.2 (DOUT), D8.4 (DIN)
unnamed: D8.2 (DOUT), D9.4 (DIN)
unnamed: D9.2 (DOUT), D10.4 (DIN)
unnamed: D10.2 (DOUT), D11.4 (DIN)
unnamed: D11.2 (DOUT), D12.4 (DIN)
unnamed: D12.2 (DOUT), D13.4 (DIN)
unnamed: D13.2 (DOUT), D14.4 (DIN)
unnamed: D14.2 (DOUT), D15.4 (DIN)

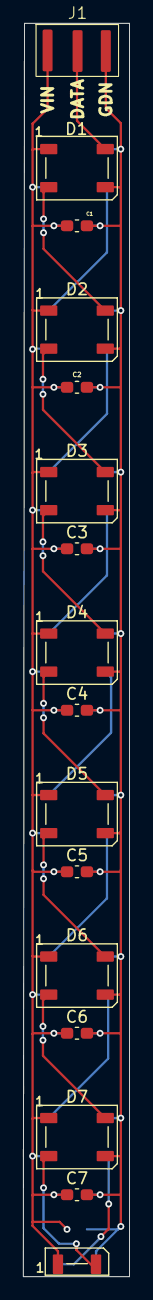
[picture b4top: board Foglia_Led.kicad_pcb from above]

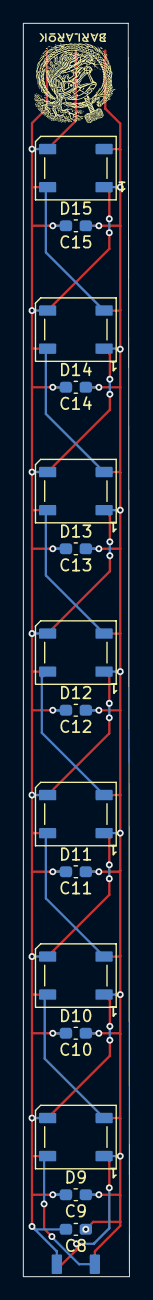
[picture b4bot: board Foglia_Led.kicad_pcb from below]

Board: 2 copper layers, 9.2 x 108.6 mm, 31 parts (15 on the bottom side), 17 nets.

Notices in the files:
README.md:
iOS App: GPL v3
